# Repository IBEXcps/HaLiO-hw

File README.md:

# Hardware design of HaLiO

Use KiCad to open the project.

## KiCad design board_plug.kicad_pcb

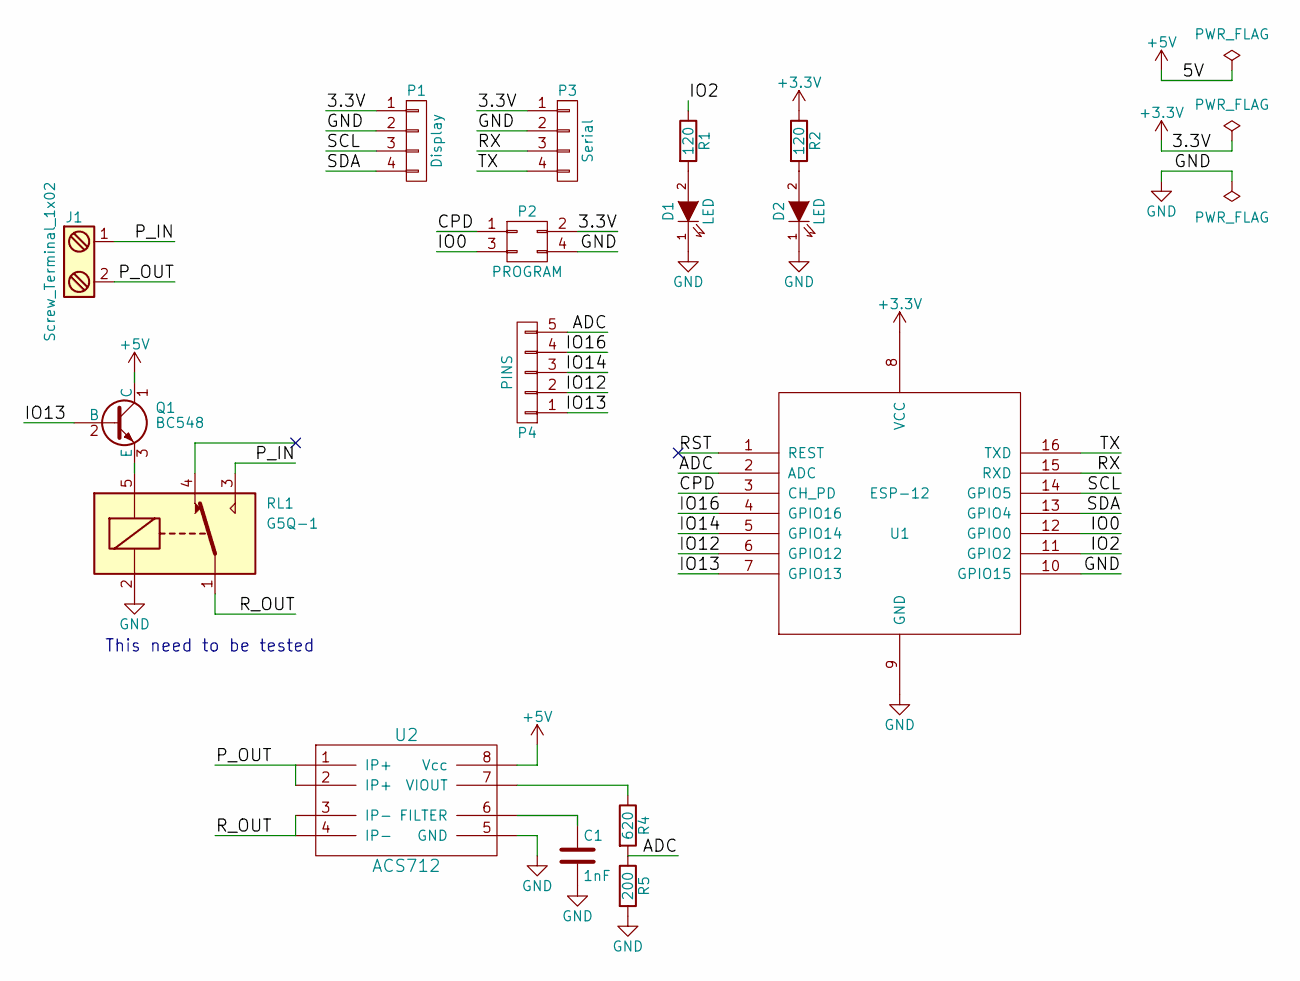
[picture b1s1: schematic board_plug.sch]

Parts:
C1: 1nF; C_Disc_D3_P2.5
D1, D2: LED; LED_0805
J1: Screw_Terminal_1x02; bornier2
P1: Display; Pin_Header_Straight_1x04
P2: PROGRAM; Pin_Header_Straight_2x02
P3: Serial; Pin_Header_Straight_1x04
P4: PINS; Pin_Header_Straight_1x05
Q1: BC548; TO-92_Inline_Narrow_Oval
R1, R2: 120; R_0805_HandSoldering
R4: 620; R_0805_HandSoldering
R5: 200; R_0805_HandSoldering
RL1: G5Q-1; Relay_SANYOU_SRD_Series_Form_C
U1: ESP-12
U2: ACS712; SOIC-8-N

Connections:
+3V3: P1.1, P2.2, P3.1, R2.1, U1.8 (VCC)
+5V: Q1.1 (C), U2.8 (Vcc)
/ADC: P4.5, R4.2, R5.1, U1.2 (ADC)
/CPD: P2.1, U1.3 (CH_PD)
/IO0: P2.3, U1.12 (GPIO0)
/IO2: R1.1, U1.11 (GPIO2)
/IO12: P4.2, U1.6 (GPIO12)
/IO13: P4.1, Q1.2 (B), U1.7 (GPIO13)
/IO14: P4.3, U1.5 (GPIO14)
/IO16: P4.4, U1.4 (GPIO16)
/P_IN: J1.1, RL1.3
/P_OUT: J1.2, U2.1 (IP+), U2.2 (IP+)
/RST: U1.1 (REST)
/RX: P3.3, U1.15 (RXD)
/R_OUT: RL1.1, U2.3 (IP-), U2.4 (IP-)
/SCL: P1.3, U1.14 (GPIO5)
/SDA: P1.4, U1.13 (GPIO4)
/TX: P3.4, U1.16 (TXD)
GND: C1.2, D1.1 (K), D2.1 (K), P1.2, P2.4, P3.2, R5.2, RL1.2, U1.9 (GND), U1.10 (GPIO15), U2.5 (GND)
unnamed: C1.1, U2.6 (FILTER)
unnamed: D1.2 (A), R1.2
unnamed: D2.2 (A), R2.2
unnamed: Q1.3 (E), RL1.5
unnamed: R4.1, U2.7 (VIOUT)

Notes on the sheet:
This need to be tested

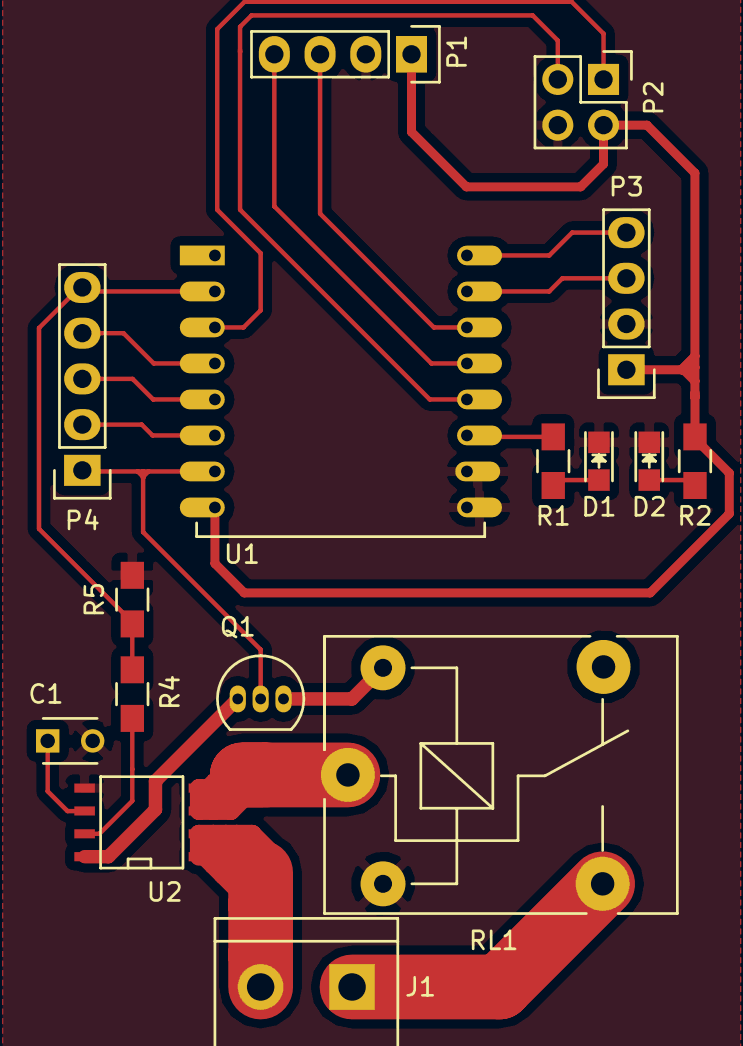
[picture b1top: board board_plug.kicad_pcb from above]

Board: 2 copper layers, 16 parts (0 on the bottom side), 23 nets.

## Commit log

2016-12-18 Add ESP8266 submodule
2016-12-18 Add initial circuit
2016-12-18 Add first board layout
2016-12-18 Add .gitignore
2017-02-04 add acs712 lib
2017-02-04 Add rescue.lib in .gitignore
2017-02-04 Add report.txt in .gitignore
2017-02-05 Add version with relay and acs
2017-09-07 Update 3D models to new version
2017-09-07 Add README.md
2017-09-07 Add LICENSE
